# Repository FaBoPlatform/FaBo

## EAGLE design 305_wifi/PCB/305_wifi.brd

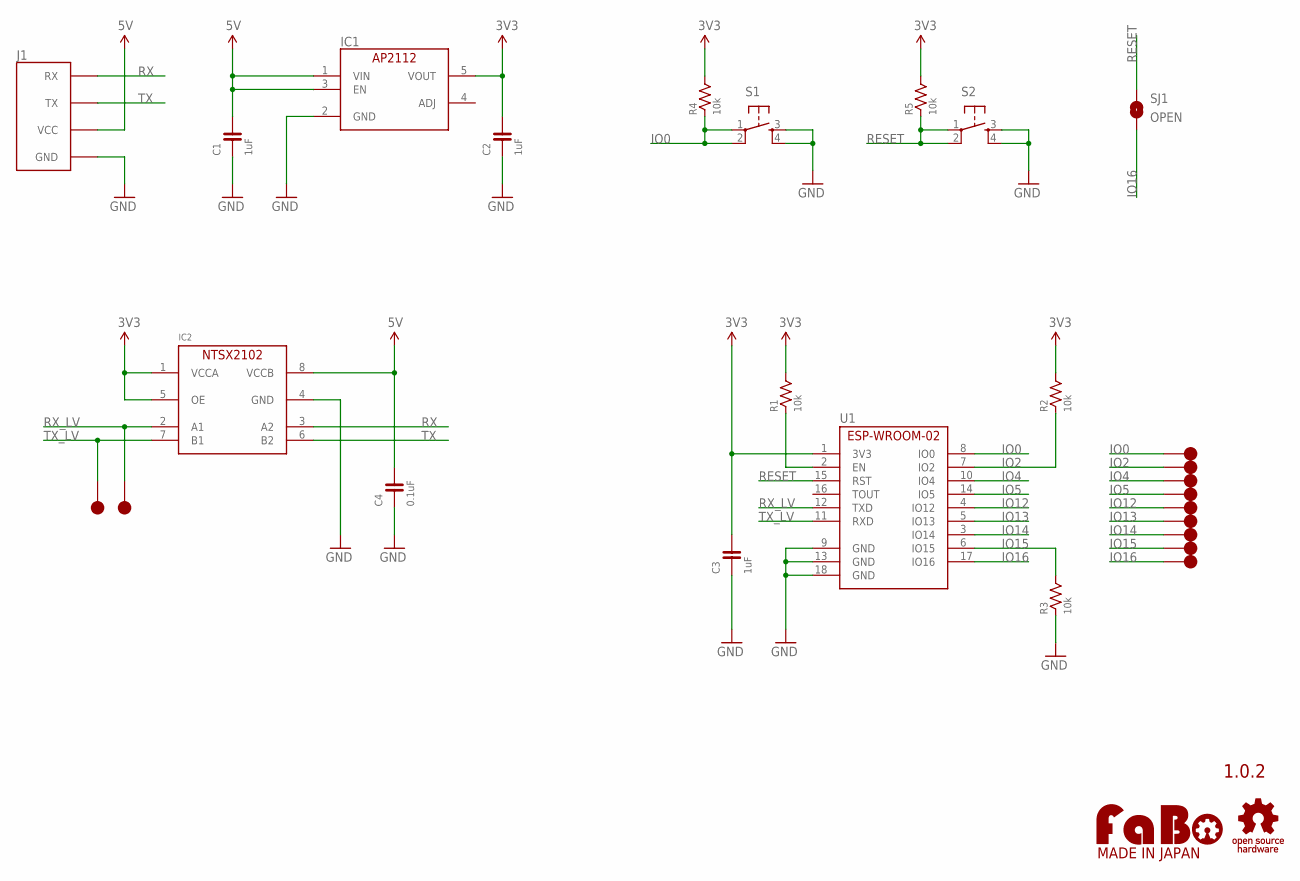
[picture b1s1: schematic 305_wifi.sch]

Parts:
C1, C2, C3: 1uF; 0603
C4: 0.1uF; 0603
IC1: AP2112K-3.3TRG1; SOT-23-5
IC2: NTSX2102GU8H; SOT1309-1
J1: FABO_BRICK_SERIAL-2_HOLE; FABO_BRICK_SERIAL_2HOLE
R1, R2, R3, R4, R5: 10k; 0603
S1, S2: TACT-SWITCH-SMD_KMR2; KMR2
SJ1: OPEN; SMD-JUMPER-2-OPEN
TP1, TP2, TP3, TP4, TP5, TP6, TP7, TP8, TP9, TP10, TP11: TP-15
U1: ES-ESPWROOM02
U$1: LOGO_OSHW-M_BOTTOM; LOGO_OSHW_M_BOTTOM
U$3: LOGO_FABO-M_BOTTOM; LOGO_FABO_MS_BOTTOM

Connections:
3V3: C2.2, C3.2, IC1.5 (VOUT), IC2.1 (VCCA), IC2.5 (OE), R1.2, R2.2, R4.2, R5.2, U1.1 (3V3)
5V: C1.2, C4.2, IC1.1 (VIN), IC1.3 (EN), IC2.8 (VCCB), J1.VCC
EN: R1.1, U1.2 (EN)
GND: C1.1, C2.1, C3.1, C4.1, IC1.2 (GND), IC2.4 (GND), J1.GND, R3.1, S1.3, S1.4, S2.3, S2.4, U1.9 (GND), U1.13 (GND), U1.18 (GND)
IO0: R4.1, S1.1, S1.2, TP1.1, U1.8 (IO0)
IO2: R2.1, TP2.1, U1.7 (IO2)
IO4: TP3.1, U1.10 (IO4)
IO5: TP4.1, U1.14 (IO5)
IO12: TP5.1, U1.4 (IO12)
IO13: TP6.1, U1.5 (IO13)
IO14: TP7.1, U1.3 (IO14)
IO15: R3.2, TP8.1, U1.6 (IO15)
IO16: SJ1.2, TP9.1, U1.17 (IO16)
RESET: R5.1, S2.1, S2.2, SJ1.1, U1.15 (RST)
RX: IC2.3 (A2), J1.RX
RX_LV: IC2.2 (A1), TP10.1, U1.12 (TXD)
TX: IC2.6 (B2), J1.TX
TX_LV: IC2.7 (B1), TP11.1, U1.11 (RXD)

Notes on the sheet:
1.0.2

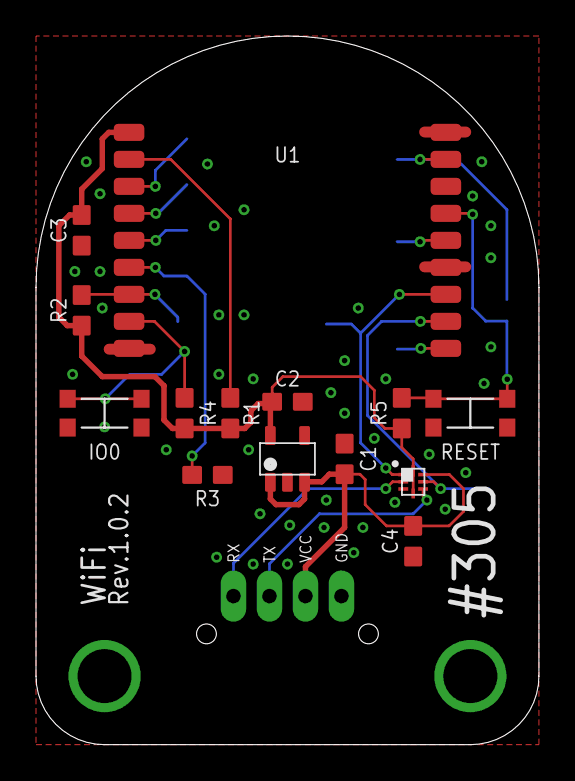
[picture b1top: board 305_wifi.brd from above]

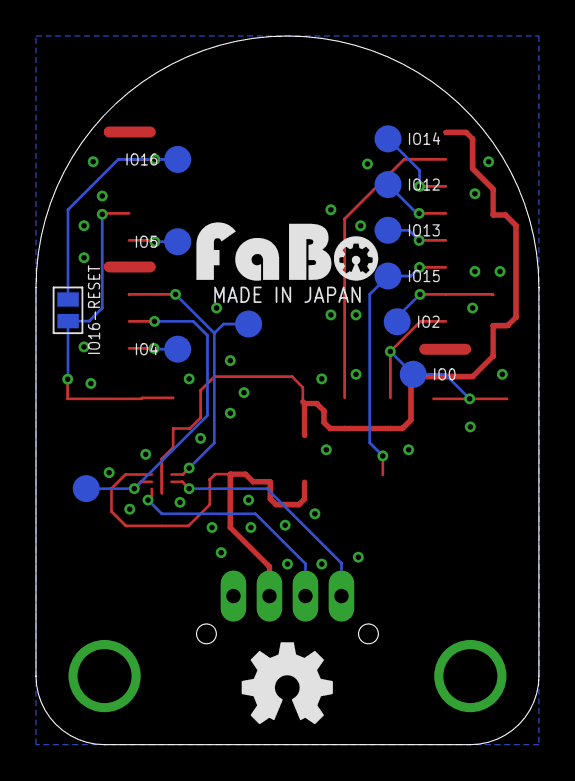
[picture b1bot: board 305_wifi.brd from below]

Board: 2 copper layers, 27.9 x 39.4 mm, 29 parts (12 on the bottom side), 18 nets.

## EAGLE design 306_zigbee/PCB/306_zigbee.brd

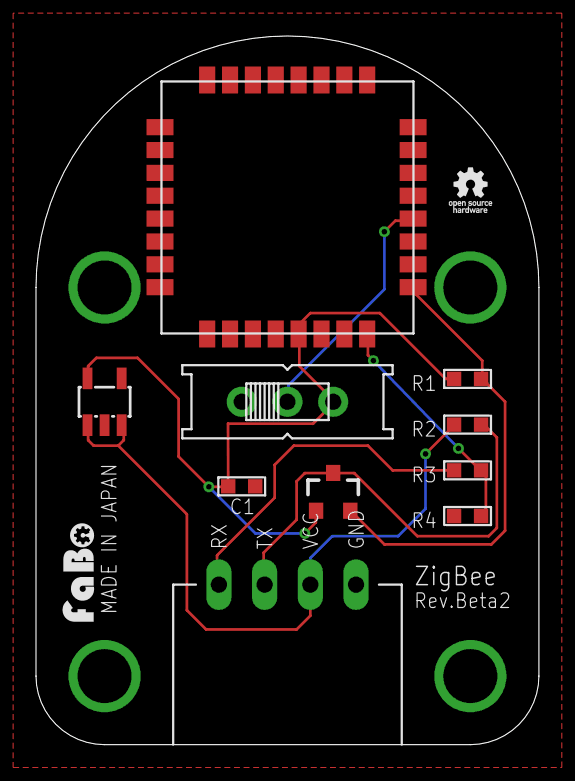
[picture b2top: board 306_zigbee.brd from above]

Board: 2 copper layers, 27.9 x 39.4 mm, 12 parts (0 on the bottom side), 8 nets.

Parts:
BSS138: SOT23-3
C1: 1uf; 0603
LP2985: SOT23-DBV
R1, R2, R3, R4: 10K; 0603
S4: SERIAL_PWR; EG1218
U$2: BRICK_SERIAL
U$3: TOCOS-TWE001L
U$4: LOGO_FABO_S
U$5: LOGO_OSHW_T_S

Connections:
+3V3: BSS138.1, C1.2, LP2985.5, R1.2, S4.S, U$3.5
+5V: LP2985.1, LP2985.3, R2.2, U$2.VCC
GND: C1.1, LP2985.2, R4.1, S4.O, U$2.GND, U$3.19, U$3.20, U$3.28, U$3.30, U$3.31, U$3.32
MODE: S4.P, U$3.12
RX_HV: R3.2, U$2.RX
RX_LV: R3.1, R4.2, U$3.8
TX_HV: BSS138.3, R2.1, U$2.TX
TX_LV: BSS138.2, R1.1, U$3.9

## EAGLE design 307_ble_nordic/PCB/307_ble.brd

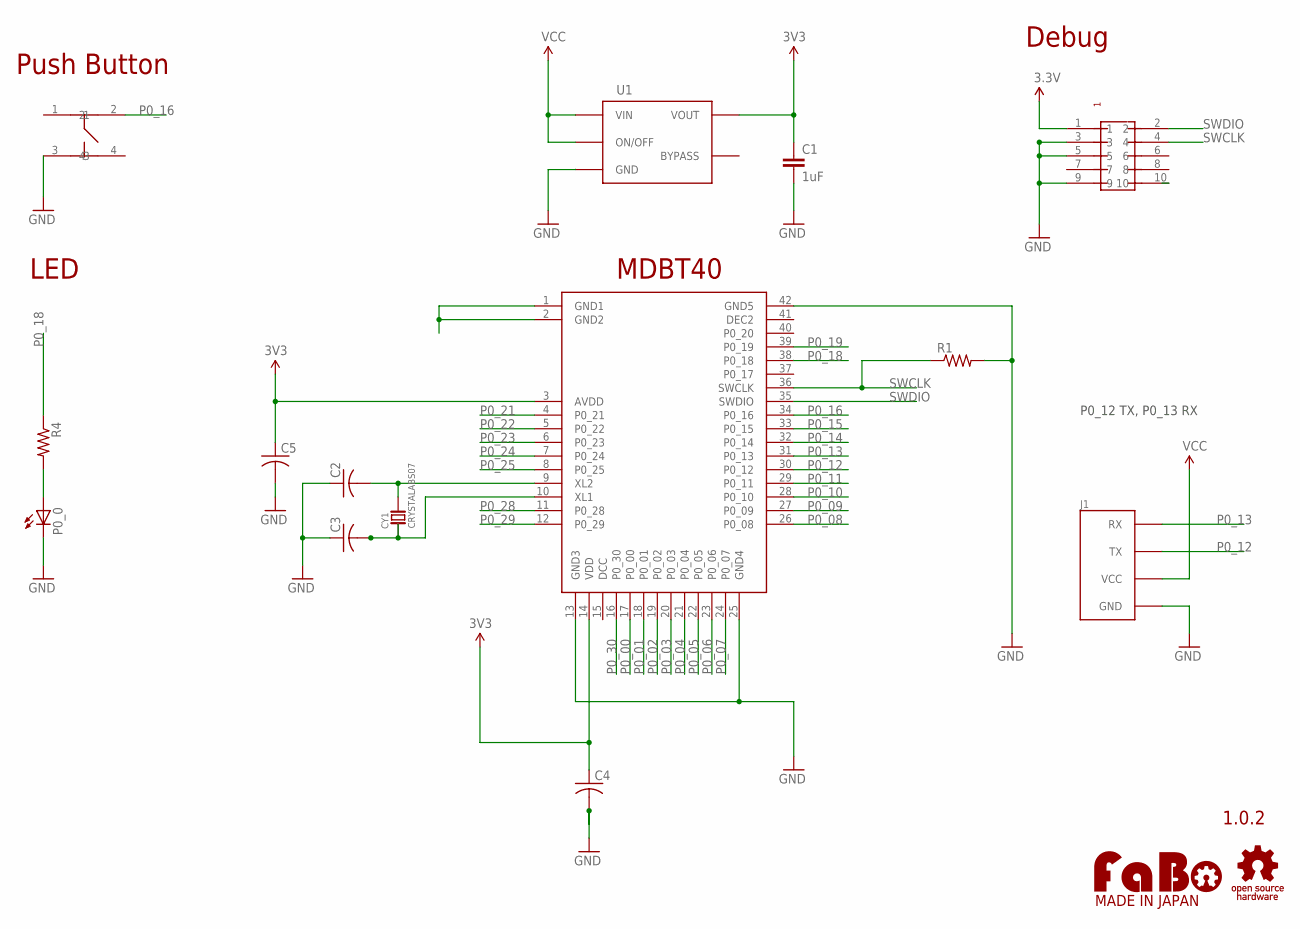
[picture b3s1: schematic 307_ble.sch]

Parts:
C1: 1uF; EIA0603
C2, C3, C4, C5: C-USC0603; C0603
CY1: CRYSTALABS07; ABRACOM-ABS07-32.768KHZ
J1: FABO_BRICK_SERIAL
P0_0: LEDCHIP-LED0603; CHIP-LED0603
R1, R4: R-US_R0603; R0603
U1: LP2985-33DBVR; SOT_23_5
U$2: LOGO_OSHW-T_M_BOTTOM; LOGO_OSHW_T_M_BOTTOM
U$3: LOGO_FABO-M_BOTTOM; LOGO_FABO_M_BOTTOM
U$6: SWICTH-4P(KMR2); SWITCH-4P(KMR2)
U$7: RAYTAC-MDBT40
U$8: PIN-HEADER-SMT(1.27MM)2X5

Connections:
3.3V: U$8.1
3V3: C1.1, C4.1, C5.1, U1.5 (VOUT), U$7.3 (AVDD), U$7.14 (VDD)
GND: C1.2, C2.1, C3.1, C4.2, C5.2, J1.GND, P0_0.C, R1.2, U1.2 (GND), U$6.3, U$7.13 (GND3), U$7.25 (GND4), U$7.42 (GND5), U$8.3, U$8.5, U$8.9
unnamed: P0_0.A, R4.2
unnamed: C2.2, CY1.P$2, U$7.9 (XL2)
unnamed: C3.2, CY1.P$1, U$7.10 (XL1)
unnamed: U$7.1 (GND1), U$7.2 (GND2)
P0_00: U$7.17 (P0_00)
P0_01: U$7.18 (P0_01)
P0_02: U$7.19 (P0_02)
P0_03: U$7.20 (P0_03)
P0_04: U$7.21 (P0_04)
P0_05: U$7.22 (P0_05)
P0_06: U$7.23 (P0_06)
P0_07: U$7.24 (P0_07)
P0_08: U$7.26 (P0_08)
P0_09: U$7.27 (P0_09)
P0_10: U$7.28 (P0_10)
P0_11: U$7.29 (P0_11)
P0_12: J1.TX, U$7.30 (P0_12)
P0_13: J1.RX, U$7.31 (P0_13)
P0_14: U$7.32 (P0_14)
P0_15: U$7.33 (P0_15)
P0_16: U$6.2, U$7.34 (P0_16)
P0_18: R4.1, U$7.38 (P0_18)
P0_19: U$7.39 (P0_19)
P0_21: U$7.4 (P0_21)
P0_22: U$7.5 (P0_22)
P0_23: U$7.6 (P0_23)
P0_24: U$7.7 (P0_24)
P0_25: U$7.8 (P0_25)
P0_28: U$7.11 (P0_28)
P0_29: U$7.12 (P0_29)
P0_30: U$7.16 (P0_30)
RESET: U$8.10
SWCLK: R1.1, U$7.36 (SWCLK), U$8.4
SWDIO: U$7.35 (SWDIO), U$8.2
VCC: J1.VCC, U1.1 (VIN), U1.3 (ON/OFF)

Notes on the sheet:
1.0.2
Push Button
MDBT40
LED
Debug
P0_12 TX, P0_13 RX

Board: 2 copper layers, 16 parts (0 on the bottom side), 13 nets, no tracks yet.

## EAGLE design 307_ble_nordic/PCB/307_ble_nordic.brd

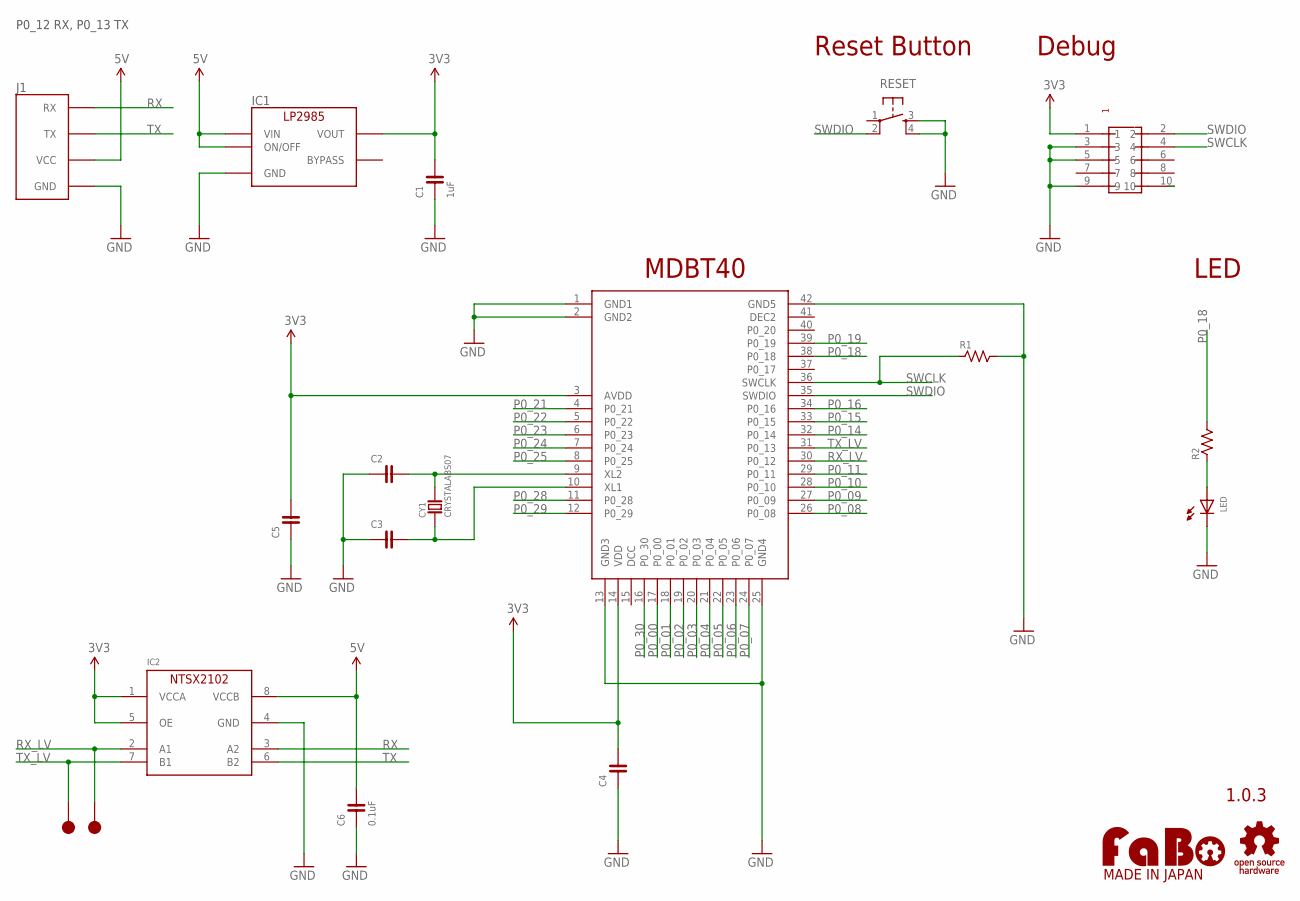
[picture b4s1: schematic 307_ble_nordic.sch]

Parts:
C1: 1uF; 0603
C2, C3: CAPACITOR-0603_NARROW; 0603-NARROW
C4, C5: CAPACITOR-0603; 0603
C6: 0.1uF; 0603
CY1: CRYSTALABS07; ABRACOM-ABS07-32.768KHZ
IC1: LP2985-33DBV; SOT-23-5
IC2: NTSX2102GU8H; SOT1309-1
J1: FABO_BRICK_SERIAL
LED: LED-0603; 0603
R1, R2: RESISTOR-0603; 0603
RESET: TACT-SWITCH-SMD_KMR2; KMR2
TP10, TP11: TP-15
U$2: LOGO_OSHW-M_BOTTOM; LOGO_OSHW_M_BOTTOM
U$3: LOGO_FABO-M_BOTTOM; LOGO_FABO_MS_BOTTOM
U$7: RAYTAC-MDBT40
U$8: PIN-HEADER-SMT(1.27MM)2X5

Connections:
3V3: C1.2, C4.2, C5.2, IC1.5 (VOUT), IC2.1 (VCCA), IC2.5 (OE), U$7.3 (AVDD), U$7.14 (VDD), U$8.1
5V: C6.2, IC1.1 (VIN), IC1.3 (ON/OFF), IC2.8 (VCCB), J1.VCC
GND: C1.1, C2.1, C3.1, C4.1, C5.1, C6.1, IC1.2 (GND), IC2.4 (GND), J1.GND, LED.CATHODE, R1.2, RESET.3, RESET.4, U$7.1 (GND1), U$7.2 (GND2), U$7.13 (GND3), U$7.25 (GND4), U$7.42 (GND5), U$8.3, U$8.5, U$8.9
unnamed: LED.ANODE, R2.1
unnamed: C2.2, CY1.P$2, U$7.9 (XL2)
unnamed: C3.2, CY1.P$1, U$7.10 (XL1)
P0_00: U$7.17 (P0_00)
P0_01: U$7.18 (P0_01)
P0_02: U$7.19 (P0_02)
P0_03: U$7.20 (P0_03)
P0_04: U$7.21 (P0_04)
P0_05: U$7.22 (P0_05)
P0_06: U$7.23 (P0_06)
P0_07: U$7.24 (P0_07)
P0_08: U$7.26 (P0_08)
P0_09: U$7.27 (P0_09)
P0_10: U$7.28 (P0_10)
P0_11: U$7.29 (P0_11)
P0_14: U$7.32 (P0_14)
P0_15: U$7.33 (P0_15)
P0_16: U$7.34 (P0_16)
P0_18: R2.2, U$7.38 (P0_18)
P0_19: U$7.39 (P0_19)
P0_21: U$7.4 (P0_21)
P0_22: U$7.5 (P0_22)
P0_23: U$7.6 (P0_23)
P0_24: U$7.7 (P0_24)
P0_25: U$7.8 (P0_25)
P0_28: U$7.11 (P0_28)
P0_29: U$7.12 (P0_29)
P0_30: U$7.16 (P0_30)
RESET: U$8.10
RX: IC2.3 (A2), J1.RX
RX_LV: IC2.2 (A1), TP10.1, U$7.30 (P0_12)
SWCLK: R1.1, U$7.36 (SWCLK), U$8.4
SWDIO: RESET.2, U$7.35 (SWDIO), U$8.2
TX: IC2.6 (B2), J1.TX
TX_LV: IC2.7 (B1), TP11.1, U$7.31 (P0_13)

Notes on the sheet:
1.0.3
Reset Button
MDBT40
LED
Debug
P0_12 RX, P0_13 TX

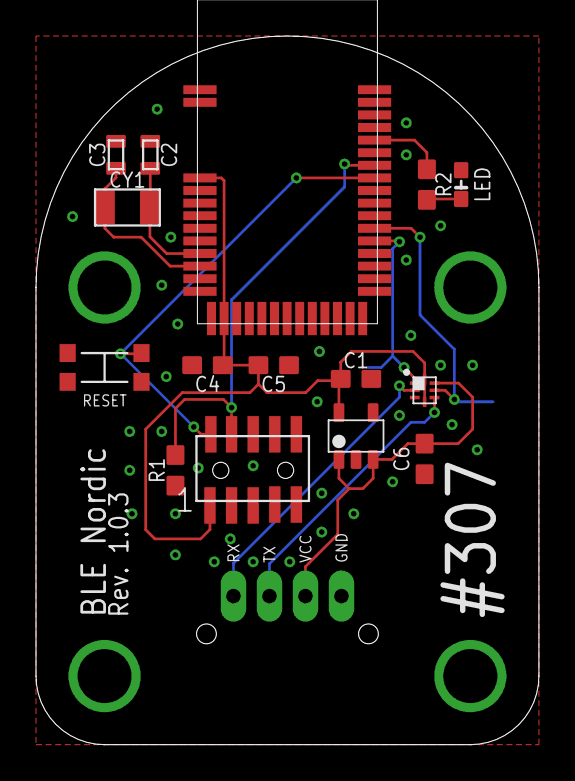
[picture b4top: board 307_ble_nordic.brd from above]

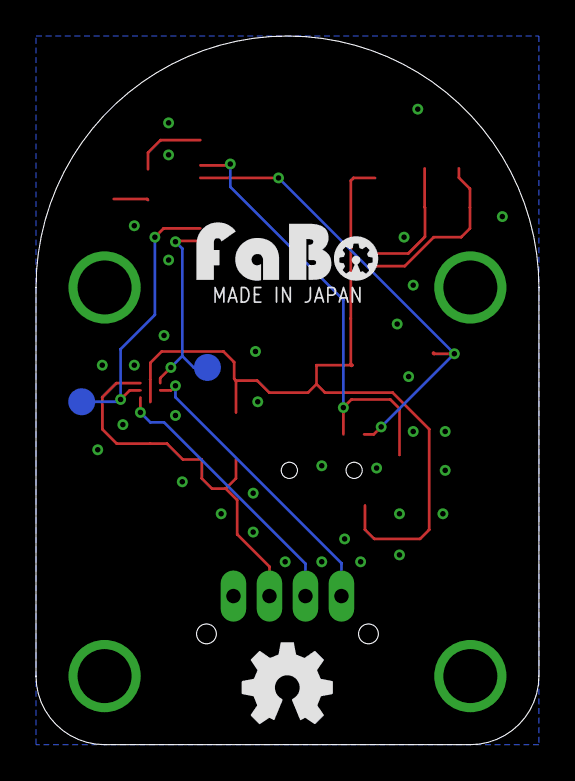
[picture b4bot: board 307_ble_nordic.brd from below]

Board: 2 copper layers, 27.9 x 39.4 mm, 20 parts (2 on the bottom side), 13 nets.

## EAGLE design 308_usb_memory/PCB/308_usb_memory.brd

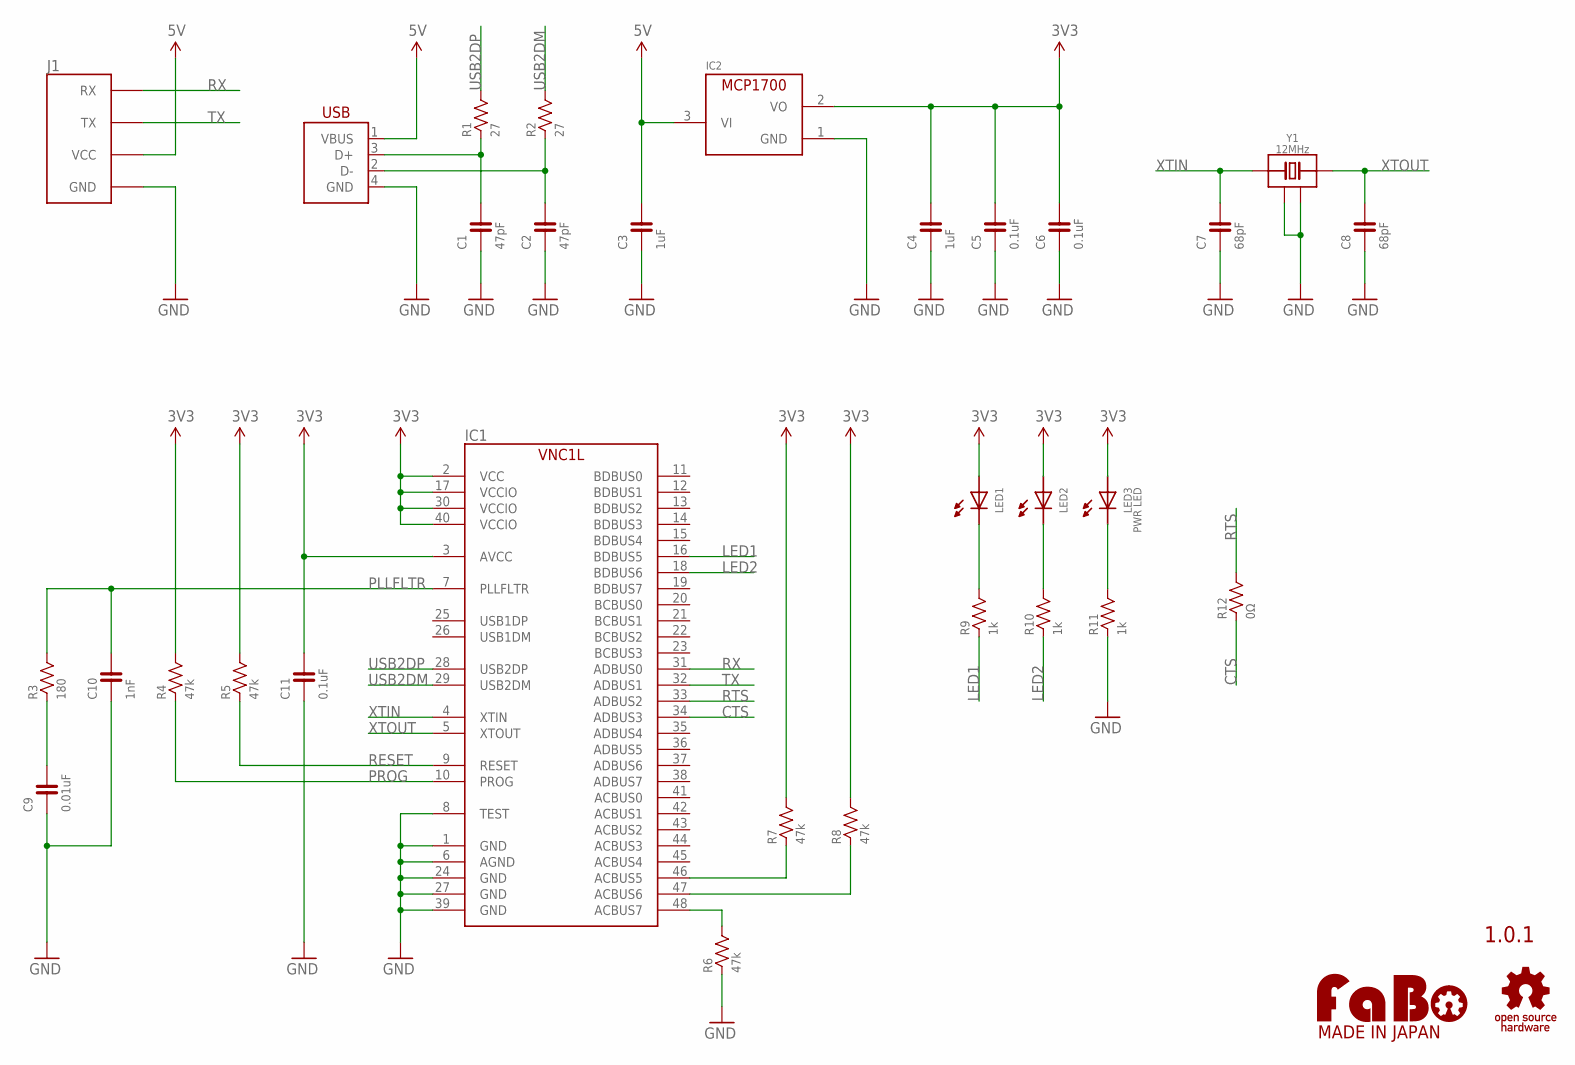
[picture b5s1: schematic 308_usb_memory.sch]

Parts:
C1, C2: 47pF; 0603-NARROW
C3, C4: 1uF; 0603-NARROW
C5, C6, C11: 0.1uF; 0603-NARROW
C7, C8: 68pF; 0603-NARROW
C9: 0.01uF; 0603-NARROW
C10: 1nF; 0603-NARROW
IC1: VNC1L-1A; LQFP-48
IC2: MCP1700T-3302TT; SOT-23
J1: FABO_BRICK_SERIAL-2_HOLE; FABO_BRICK_SERIAL_2HOLE
LED1, LED2: LED-0603-NARROW; 0603-NARROW
LED3: PWR LED; 0603-NARROW
R1, R2: 27; 0603-NARROW
R3: 180; 0603-NARROW
R4, R5, R6, R7, R8: 47k; 0603-NARROW
R9, R10, R11: 1k; 0603-NARROW
R12: 0Ω; 0603-NARROW
U$2: LOGO_FABO-M_BOTTOM; LOGO_FABO_MS_BOTTOM
U$3: LOGO_OSHW-M_BOTTOM; LOGO_OSHW_M_BOTTOM
USB1: USB-B_PTH; USB-4AF103BS
Y1: 12MHz; ECS-12MHZ

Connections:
3V3: C4.2, C5.2, C6.2, C11.2, IC1.2 (VCC), IC1.3 (AVCC), IC1.17 (VCCIO), IC1.30 (VCCIO), IC1.40 (VCCIO), IC2.2 (VO), LED1.ANODE, LED2.ANODE, LED3.ANODE, R4.2, R5.2, R7.2, R8.2
5V: C3.2, IC2.3 (VI), J1.VCC, USB1.1 (VBUS)
ACBUS5: IC1.46 (ACBUS5), R7.1
ACBUS6: IC1.47 (ACBUS6), R8.1
ACBUS7: IC1.48 (ACBUS7), R6.2
CTS: IC1.34 (ADBUS3), R12.1
GND: C1.1, C2.1, C3.1, C4.1, C5.1, C6.1, C7.1, C8.1, C9.1, C10.1, C11.1, IC1.1 (GND), IC1.6 (AGND), IC1.8 (TEST), IC1.24 (GND), IC1.27 (GND), IC1.39 (GND), IC2.1 (GND), J1.GND, R6.1, R11.1, USB1.4 (GND), Y1.2 (GND), Y1.4 (GND)
LED1: IC1.16 (BDBUS5), R9.1
LED2: IC1.18 (BDBUS6), R10.1
unnamed: C9.2, R3.1
unnamed: C1.2, R1.1, USB1.3 (D+)
unnamed: C2.2, R2.1, USB1.2 (D-)
unnamed: LED2.CATHODE, R10.2
unnamed: LED1.CATHODE, R9.2
unnamed: LED3.CATHODE, R11.2
PLLFLTR: C10.2, IC1.7 (PLLFLTR), R3.2
PROG: IC1.10 (PROG), R4.1
RESET: IC1.9 (RESET), R5.1
RTS: IC1.33 (ADBUS2), R12.2
RX: IC1.31 (ADBUS0), J1.RX
TX: IC1.32 (ADBUS1), J1.TX
USB2DM: IC1.29 (USB2DM), R2.2
USB2DP: IC1.28 (USB2DP), R1.2
XTIN: C7.2, IC1.4 (XTIN), Y1.1 (IO)
XTOUT: C8.2, IC1.5 (XTOUT), Y1.3 (IO)

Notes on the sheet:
1.0.1

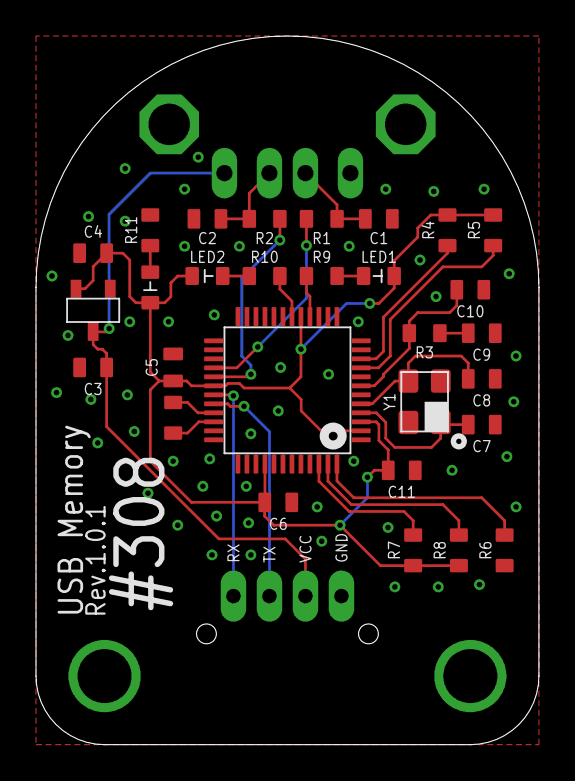
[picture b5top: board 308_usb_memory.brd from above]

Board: 2 copper layers, 27.9 x 39.4 mm, 33 parts (0 on the bottom side), 25 nets.

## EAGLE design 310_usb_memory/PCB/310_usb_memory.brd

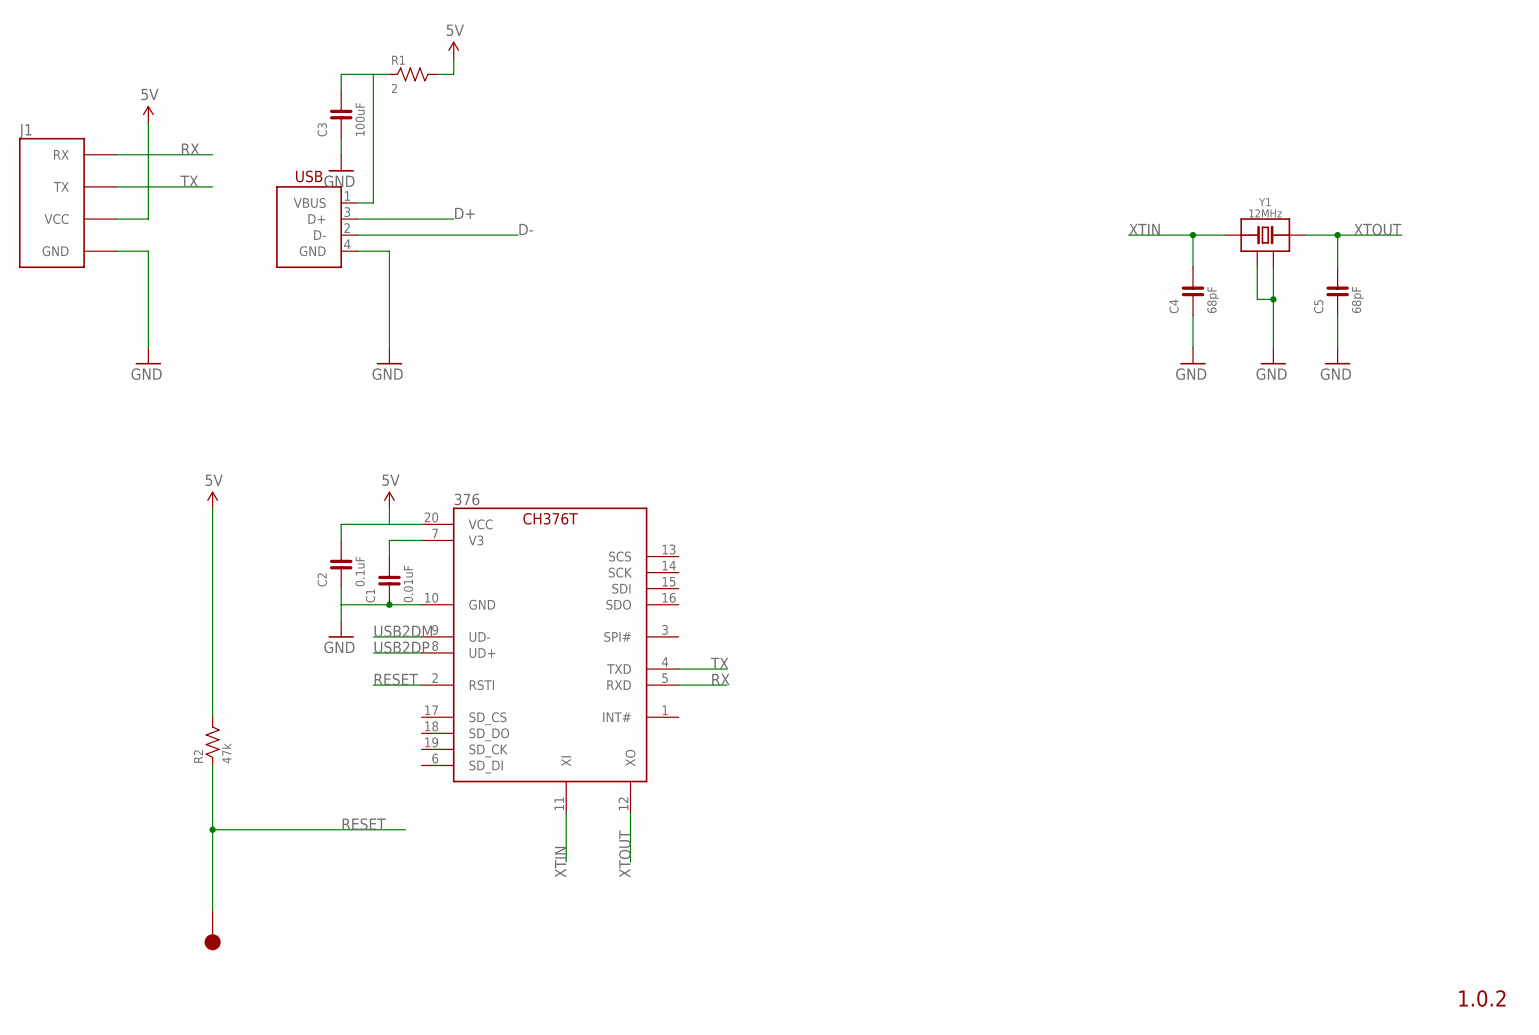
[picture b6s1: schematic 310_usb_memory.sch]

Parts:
376: CH376T; SSOP-20
C1: 0.01uF; 0402
C2: 0.1uF; 0402
C3: 100uF; 0402
C4, C5: 68pF; 0402
J1: FABO_BRICK_SERIAL
R1: 2; 0402
R2: 47k; 0402
TP1: TP-15
USB1: USB-B_PTH; USB-4AF103BS
Y1: 12MHz; ECS-12MHZ

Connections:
5V: 376.20 (VCC), C2.P$2 (2), J1.VCC, R1.P$2 (2), R2.P$2 (2)
D+: USB1.3 (D+)
D-: USB1.2 (D-)
GND: 376.10 (GND), C1.P$1 (1), C2.P$1 (1), C3.P$1 (1), C4.P$1 (1), C5.P$1 (1), J1.GND, USB1.4 (GND), Y1.2 (GND), Y1.4 (GND)
unnamed: 376.7 (V3), C1.P$2 (2)
unnamed: C3.P$2 (2), R1.P$1 (1), USB1.1 (VBUS)
RESET: 376.2 (RSTI), R2.P$1 (1), TP1.1
RX: 376.5 (RXD), J1.RX
TX: 376.4 (TXD), J1.TX
USB2DM: 376.9 (UD-)
USB2DP: 376.8 (UD+)
XTIN: 376.11 (XI), C4.P$2 (2), Y1.1 (IO)
XTOUT: 376.12 (XO), C5.P$2 (2), Y1.3 (IO)

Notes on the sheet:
1.0.2

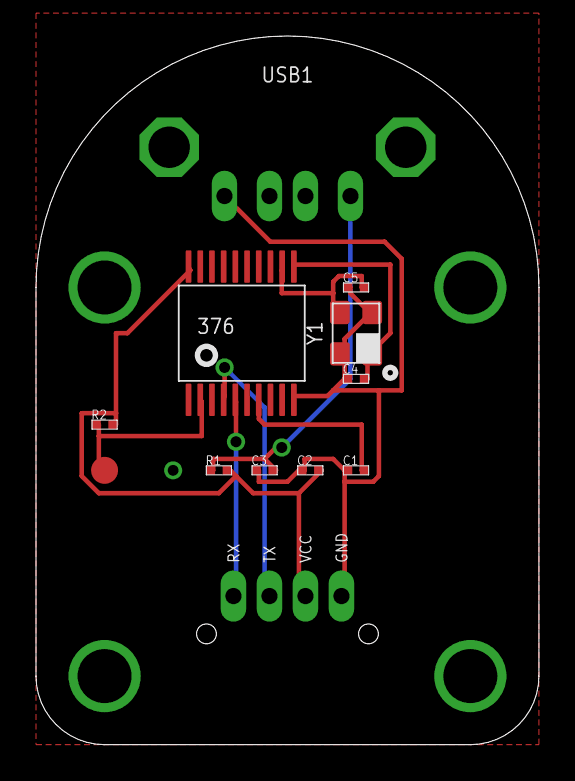
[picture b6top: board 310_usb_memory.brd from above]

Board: 2 copper layers, 27.9 x 39.4 mm, 12 parts (0 on the bottom side), 9 nets.

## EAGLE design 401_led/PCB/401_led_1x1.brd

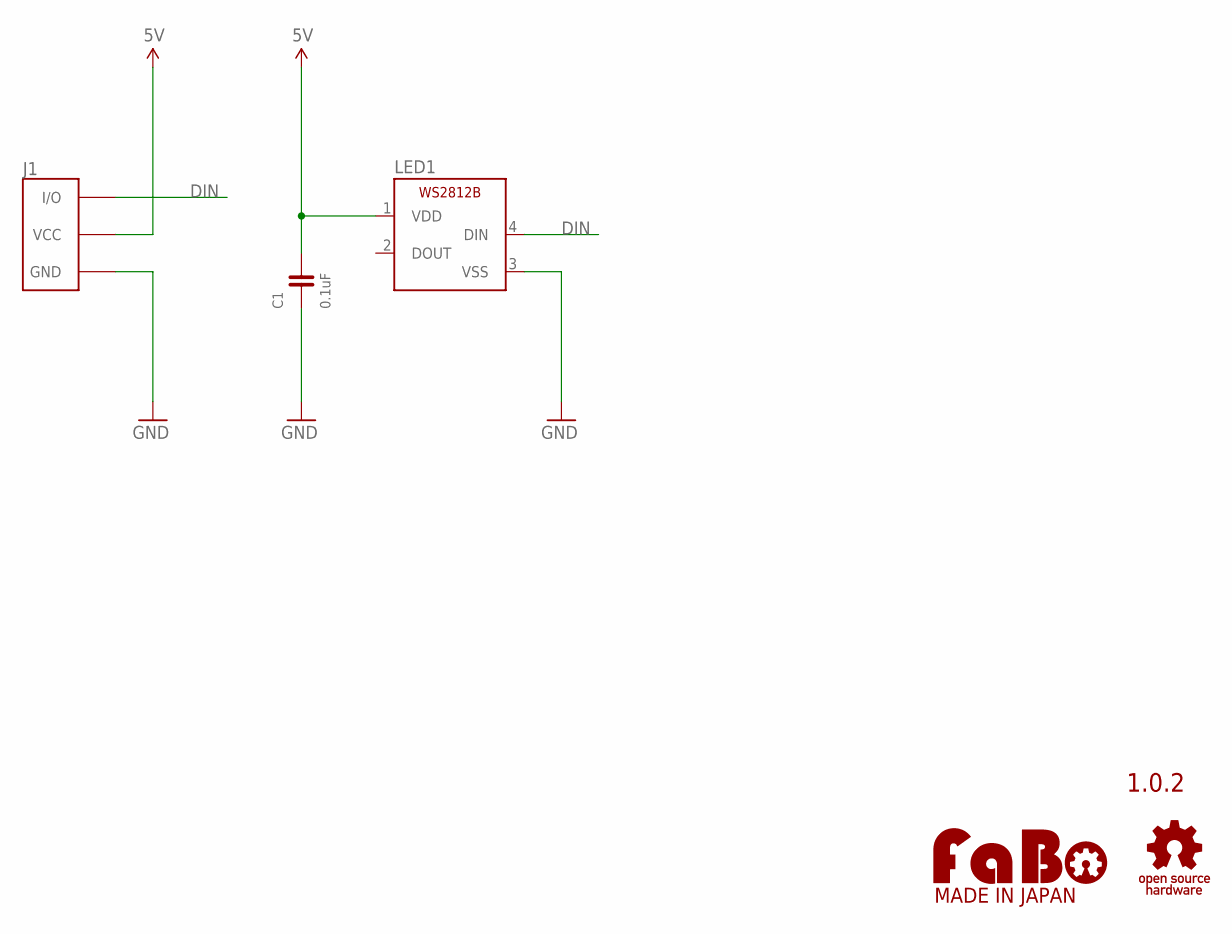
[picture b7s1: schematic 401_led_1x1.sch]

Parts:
C1: 0.1uF; 0603
J1: FABO_BRICK_3PIN
LED1: WS2812B
U$2: LOGO_OSHW-T_M_BOTTOM; LOGO_OSHW_T_MS_BOTTOM
U$3: LOGO_FABO-M; LOGO_FABO_MS

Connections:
5V: C1.2, J1.VCC, LED1.1 (VDD)
DIN: J1.IN/OUT (I/O), LED1.4 (DIN)
GND: C1.1, J1.GND, LED1.3 (VSS)

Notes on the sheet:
1.0.2

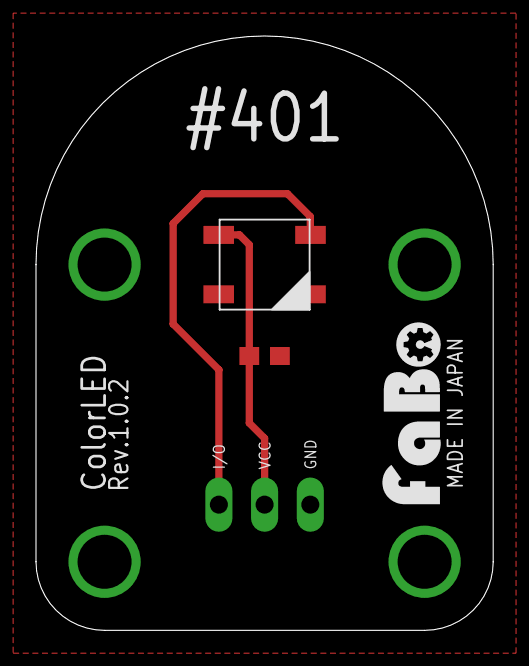
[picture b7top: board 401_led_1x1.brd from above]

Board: 2 copper layers, 25.4 x 33.0 mm, 5 parts (0 on the bottom side), 3 nets.

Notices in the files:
parts and their libraries:
FaBo-Supply: Released under the Creative Commons Attribution-ShareAlike 4.0 License
https://creativecommons.org/licenses/by-sa/4.0
FaBo-etc: Released under the Creative Commons
SparkFun: Licensing: CC v3.0 Share-Alike You are welcome to use this library for commercial purposes.
